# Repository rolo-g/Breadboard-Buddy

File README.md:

# Breadboard-Buddy

The schematic and PCB can be viewed without installing KiCad 8.0 by using [KiCanvas, an online KiCad viewer](https://github.com/theacodes/kicanvas)

https://kicanvas.org/?github=https%3A%2F%2Fgithub.com%2Frolo-g%2FBreadboard-Buddy

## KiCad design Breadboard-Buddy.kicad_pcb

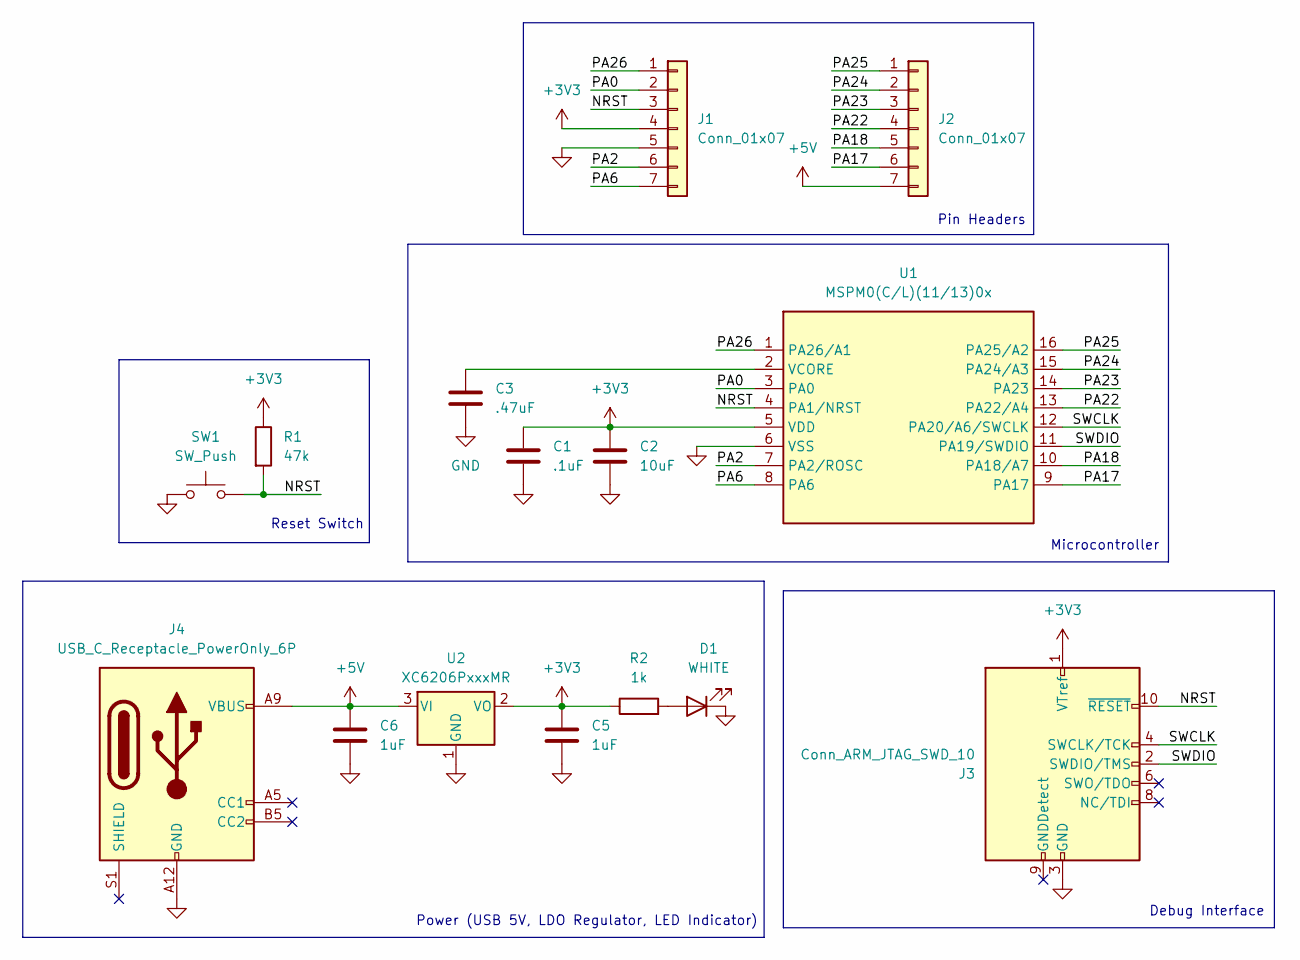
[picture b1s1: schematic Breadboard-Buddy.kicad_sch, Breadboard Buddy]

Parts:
C1: .1uF; C_0402_1005Metric; LCSC C52923
C2: 10uF; C_0603_1608Metric; LCSC C19702
C3: .47uF; C_0603_1608Metric; LCSC C1623
C5, C6: 1uF; C_0402_1005Metric; LCSC C52923
D1: WHITE; LED_0603_1608Metric; LCSC C965808
J1, J2: Conn_01x07; PinHeader_1x07_P2.54mm_Vertical
J3: Conn_ARM_JTAG_SWD_10; PinHeader_2x05_P1.27mm_Vertical_SMD; LCSC C6332249
J4: USB_C_Receptacle_PowerOnly_6P; USB_C_Receptacle_GCT_USB4125-xx-x_6P_TopMnt_Horizontal; LCSC C668623
R1: 47k; R_0402_1005Metric; LCSC C25792
R2: 1k; R_0402_1005Metric; LCSC C11702
SW1: SW_Push; SW_SPST_B3U-1000P; LCSC C231329
U1: MSPM0(C/L)(11/13)0x; Texas_DYY0016A_TSOT-23-16_4.2x2.0mm_P0.5mm
U2: XC6206PxxxMR; SOT-23-3; LCSC C347376

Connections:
+3V3: C1.1, C2.1, C5.1, J1.4, J3.1 (VTref), R1.1, R2.1, U1.5 (VDD), U2.2 (VO)
+5V: C6.1, J2.7, J4.A9 (VBUS), J4.B9 (VBUS), U2.3 (VI)
/NRST: J1.3, J3.10 (~RESET), R1.2, SW1.2, U1.4 (PA1/NRST)
/PA0: J1.2, U1.3 (PA0)
/PA2: J1.6, U1.7 (PA2/ROSC)
/PA6: J1.7, U1.8 (PA6)
/PA17: J2.6, U1.9 (PA17)
/PA18: J2.5, U1.10 (PA18/A7)
/PA22: J2.4, U1.13 (PA22/A4)
/PA23: J2.3, U1.14 (PA23)
/PA24: J2.2, U1.15 (PA24/A3)
/PA25: J2.1, U1.16 (PA25/A2)
/PA26: J1.1, U1.1 (PA26/A1)
/SWCLK: J3.4 (SWCLK/TCK), U1.12 (PA20/A6/SWCLK)
/SWDIO: J3.2 (SWDIO/TMS), U1.11 (PA19/SWDIO)
GND: C1.2, C2.2, C3.2, C5.2, C6.2, D1.1 (K), J1.5, J3.3 (GND), J3.5 (GND), J4.A12 (GND), J4.B12 (GND), SW1.1, U1.6 (VSS), U2.1 (GND)
unnamed: D1.2 (A), R2.2
unnamed: C3.1, U1.2 (VCORE)

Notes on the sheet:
Reset Switch
Pin Headers
Debug Interface
Microcontroller
Power (USB 5V, LDO Regulator, LED Indicator)

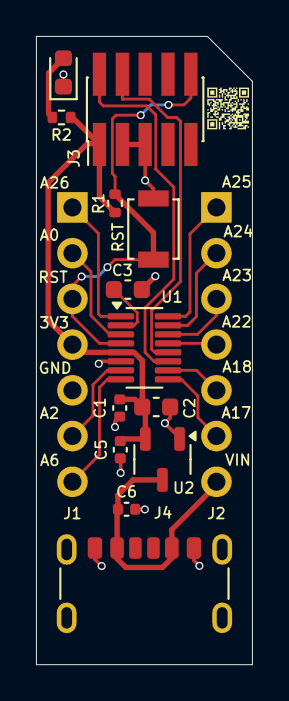
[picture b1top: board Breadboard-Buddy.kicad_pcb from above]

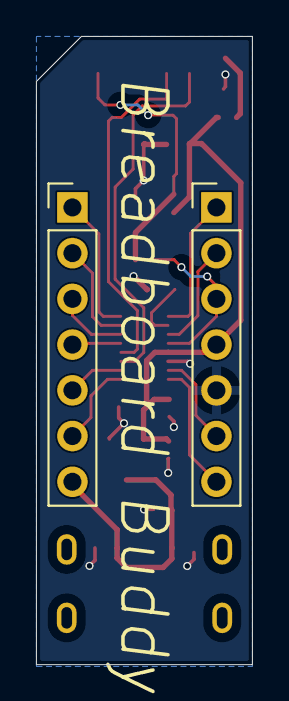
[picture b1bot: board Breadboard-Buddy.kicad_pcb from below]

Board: 2 copper layers, 12.0 x 34.9 mm, 15 parts (2 on the bottom side), 18 nets.

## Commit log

2024-10-06 Create LICENSE
